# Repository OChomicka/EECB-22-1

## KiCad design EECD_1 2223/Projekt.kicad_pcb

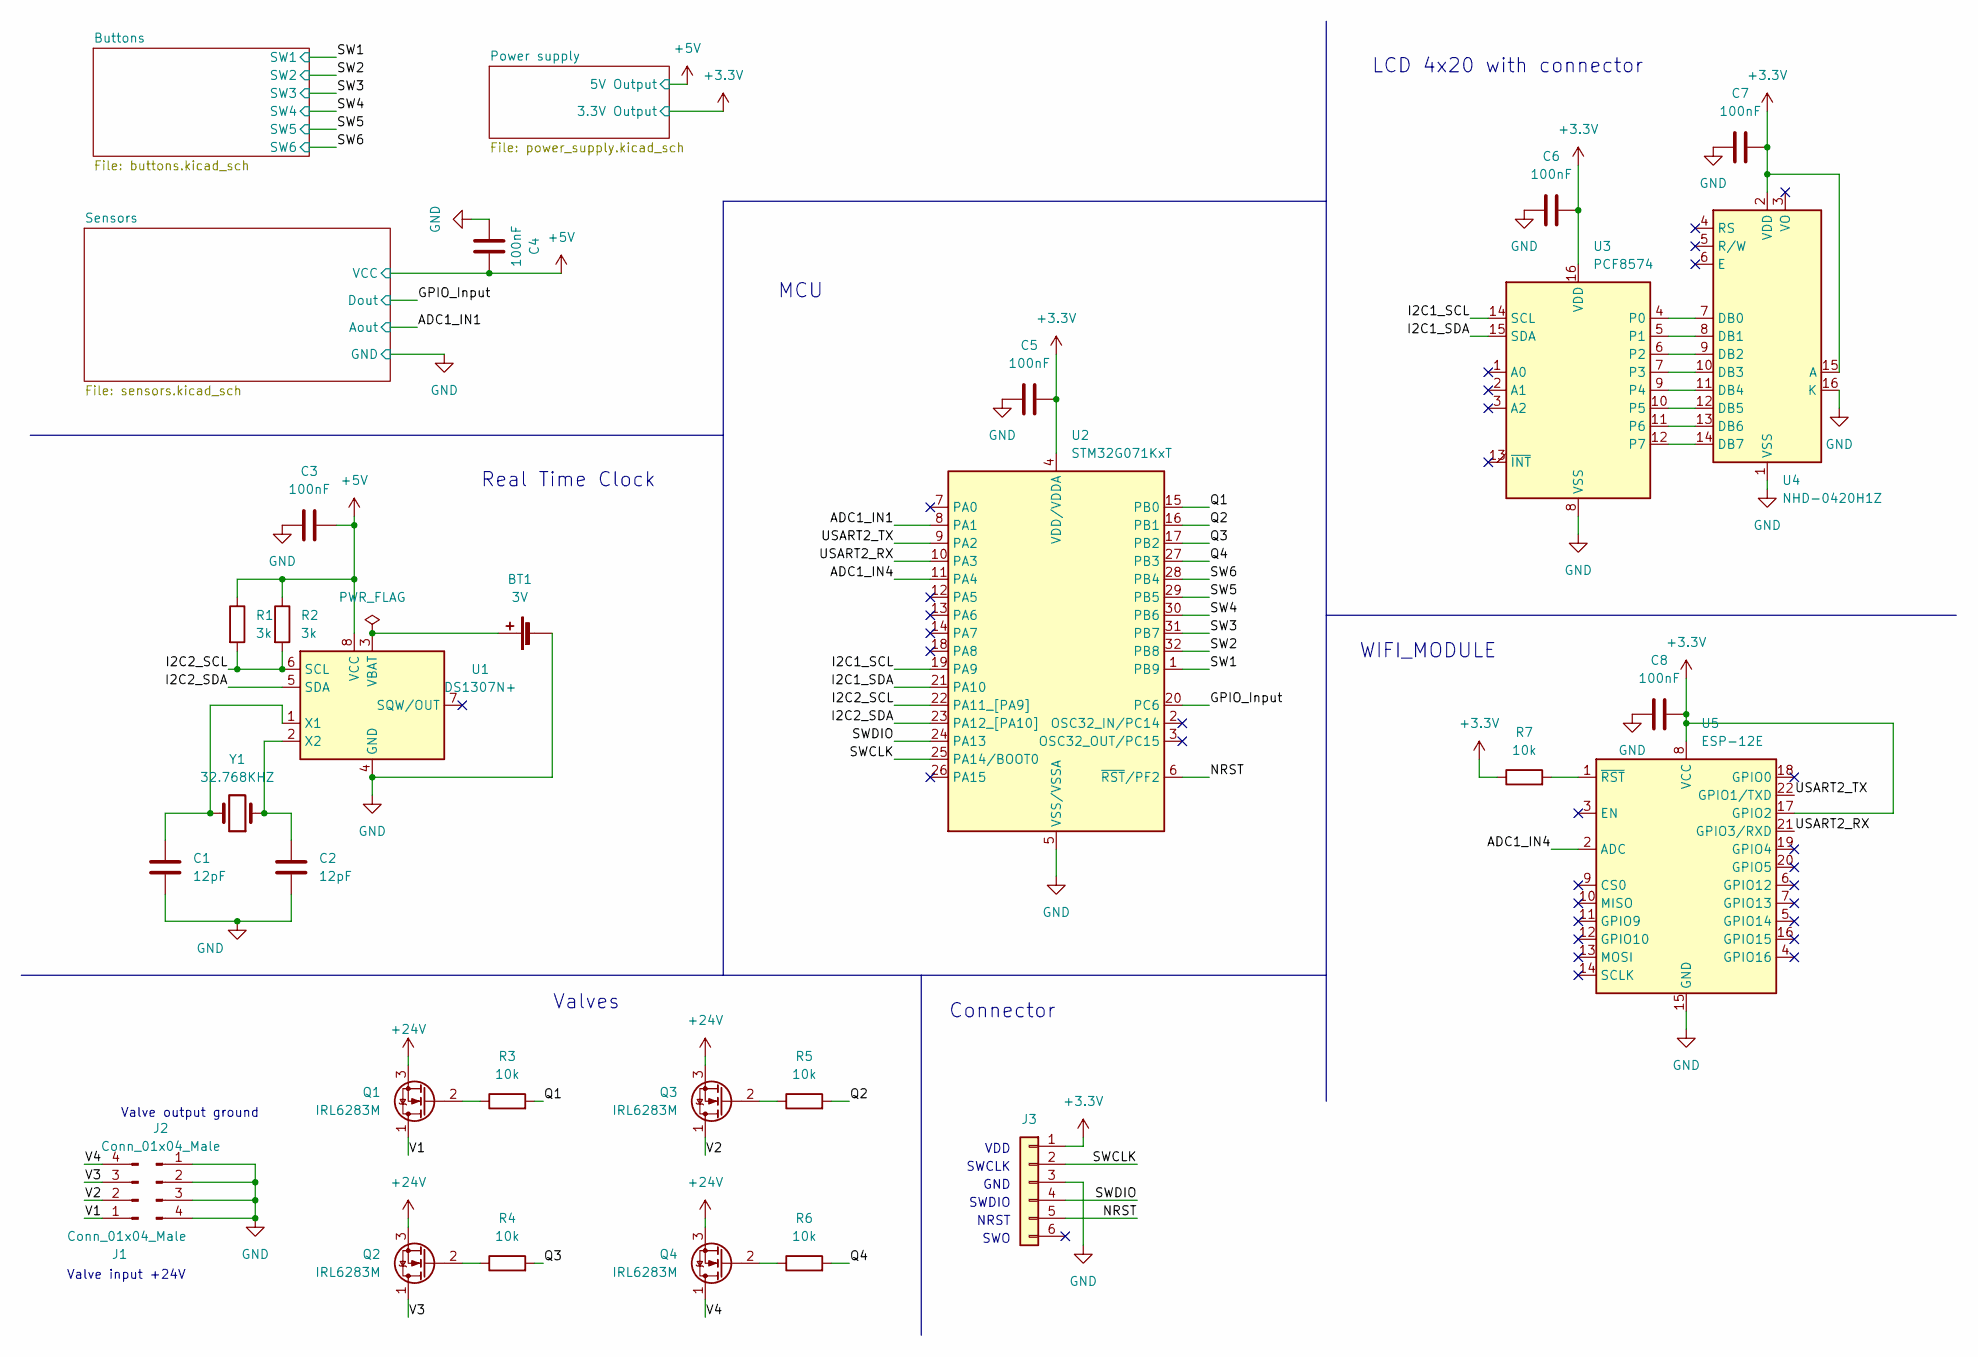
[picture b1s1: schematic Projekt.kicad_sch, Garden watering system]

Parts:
BT1: 3V; BatteryHolder_Keystone_500
C1, C2: 12pF; C_0603_1608Metric
C3, C4, C5, C6, C7, C8: 100nF; C_0603_1608Metric
J1, J2: Conn_01x04_Male; TerminalBlock_Phoenix_PT-1,5-4-3.5-H_1x04_P3.50mm_Horizontal
J3: Conn_01x06; PinHeader_1x06_P1.00mm_Vertical_SMD_Pin1Right
Q1, Q2, Q3, Q4: IRL6283M; DirectFET_MD
R1, R2: 3k; R_0603_1608Metric
R3, R4, R5, R6, R7: 10k; R_0603_1608Metric
U1: DS1307N+; SO-8_3.9x4.9mm_P1.27mm
U2: STM32G071KxT; LQFP-32_7x7mm_P0.8mm
U3: PCF8574; SO-16_3.9x9.9mm_P1.27mm
U4: NHD-0420H1Z
U5: ESP-12E
Y1: 32.768KHZ; Crystal_SMD_FOX_FQ7050-2Pin_7.0x5.0mm

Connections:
+3.3V: C5.1, C6.1, C7.1, C8.1, J3.1, R7.1, U2.4 (VDD/VDDA), U3.16 (VDD), U4.2 (VDD), U4.15 (A), U5.8 (VCC), U5.17 (GPIO2); also elsewhere on the board
+5V: C3.1, C4.1, R1.1, R2.1, U1.8 (VCC); also elsewhere on the board
+24V: Q1.3 (S), Q2.3 (S), Q3.3 (S), Q4.3 (S); also elsewhere on the board
/ADC1_IN1: U2.8 (PA1); also elsewhere on the board
/ADC1_IN4: U2.11 (PA4), U5.2 (ADC)
/GPIO_Input: U2.20 (PC6); also elsewhere on the board
/I2C1_SCL: U2.19 (PA9), U3.14 (SCL)
/I2C1_SDA: U2.21 (PA10), U3.15 (SDA)
/I2C2_SCL: R1.2, R2.2, U1.6 (SCL), U2.22 (PA11_[PA9])
/I2C2_SDA: U1.5 (SDA), U2.23 (PA12_[PA10])
/NRST: J3.5, U2.6 (~RST/PF2)
/Q1: R3.2, U2.15 (PB0)
/Q2: R5.2, U2.16 (PB1)
/Q3: R4.2, U2.17 (PB2)
/Q4: R6.2, U2.27 (PB3)
/SW1: U2.1 (PB9); also elsewhere on the board
/SW2: U2.32 (PB8); also elsewhere on the board
/SW3: U2.31 (PB7); also elsewhere on the board
/SW4: U2.30 (PB6); also elsewhere on the board
/SW5: U2.29 (PB5); also elsewhere on the board
/SW6: U2.28 (PB4); also elsewhere on the board
/SWCLK: J3.2, U2.25 (PA14/BOOT0)
/SWDIO: J3.4, U2.24 (PA13)
/USART2_RX: U2.10 (PA3), U5.21 (GPIO3/RXD)
/USART2_TX: U2.9 (PA2), U5.22 (GPIO1/TXD)
/V1: J1.1, Q1.1 (D)
/V2: J1.2, Q3.1 (D)
/V3: J1.3, Q2.1 (D)
/V4: J1.4, Q4.1 (D)
GND: BT1.2 (-), C1.2, C2.2, C3.2, C4.2, C5.2, C6.2, C7.2, C8.2, J2.1, J2.2, J2.3, J2.4, J3.3, U1.4 (GND), U2.5 (VSS/VSSA), U3.8 (VSS), U4.1 (VSS), U4.16 (K), U5.15 (GND); also elsewhere on the board
unnamed: BT1.1 (+), U1.3 (VBAT)
unnamed: C1.1, U1.1 (X1), Y1.2
unnamed: C2.1, U1.2 (X2), Y1.1
unnamed: Q1.2 (G), R3.1
unnamed: Q2.2 (G), R4.1
unnamed: Q3.2 (G), R5.1
unnamed: Q4.2 (G), R6.1
unnamed: R7.2, U5.1 (~RST)
unnamed: U3.4 (P0), U4.7 (DB0)
unnamed: U3.5 (P1), U4.8 (DB1)
unnamed: U3.6 (P2), U4.9 (DB2)
unnamed: U3.7 (P3), U4.10 (DB3)
unnamed: U3.9 (P4), U4.11 (DB4)
unnamed: U3.10 (P5), U4.12 (DB5)
unnamed: U3.11 (P6), U4.13 (DB6)
unnamed: U3.12 (P7), U4.14 (DB7)

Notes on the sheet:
Valves
VDD
SWDIO
Valve input +24V
Connector
NRST
SWCLK
MCU
Valve output ground
Real Time Clock
LCD 4x20 with connector
GND
WIFI_MODULE
SWO

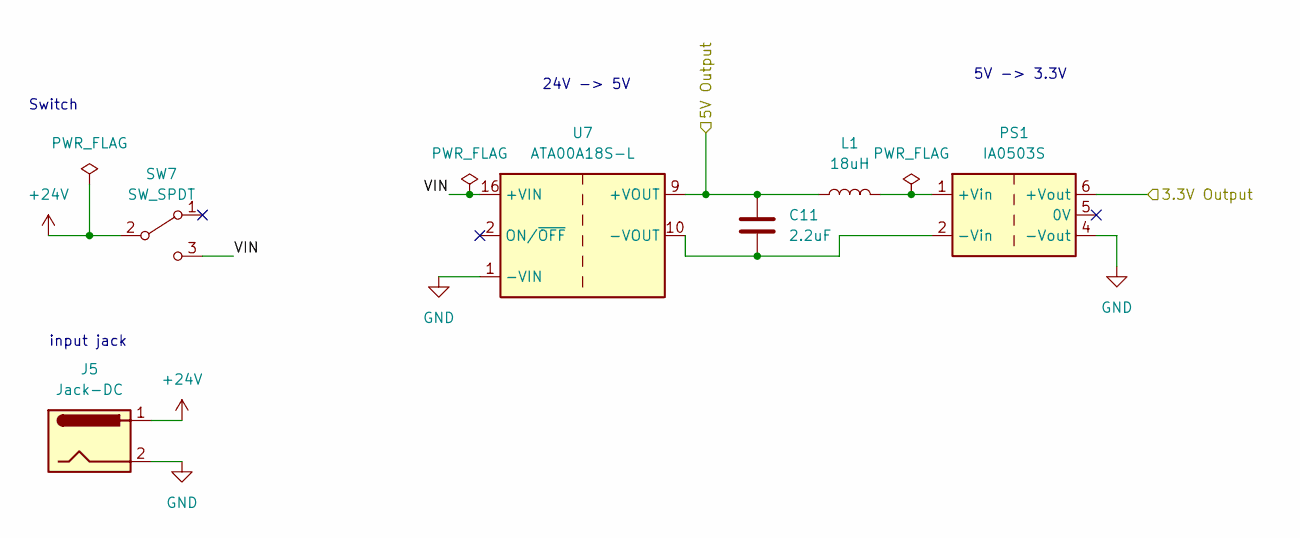
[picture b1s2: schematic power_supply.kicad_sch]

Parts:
C11: 2.2uF; C_0402_1005Metric
J5: Jack-DC; BarrelJack_CUI_PJ-063AH_Horizontal_CircularHoles
L1: 18uH; L_0603_1608Metric
PS1: IA0503S; Converter_DCDC_XP_POWER-IAxxxxS_THT
SW7: SW_SPDT; SW_Slide_1P2T_CK_OS102011MS2Q
U7: ATA00A18S-L; Converter_DCDC_Artesyn_ATA_SMD

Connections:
+3.3V: PS1.6 (+Vout); also elsewhere on the board
+5V: C11.1, L1.1, U7.9 (+VOUT); also elsewhere on the board
+24V: J5.1, SW7.2 (B); also elsewhere on the board
/Power supply/VIN: SW7.3 (C), U7.16 (+VIN)
GND: J5.2, PS1.4 (-Vout), U7.1 (-VIN); also elsewhere on the board
unnamed: C11.2, PS1.2 (-Vin), U7.10 (-VOUT)
unnamed: L1.2, PS1.1 (+Vin)

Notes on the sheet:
5V -> 3.3V
input jack
Switch
24V -> 5V

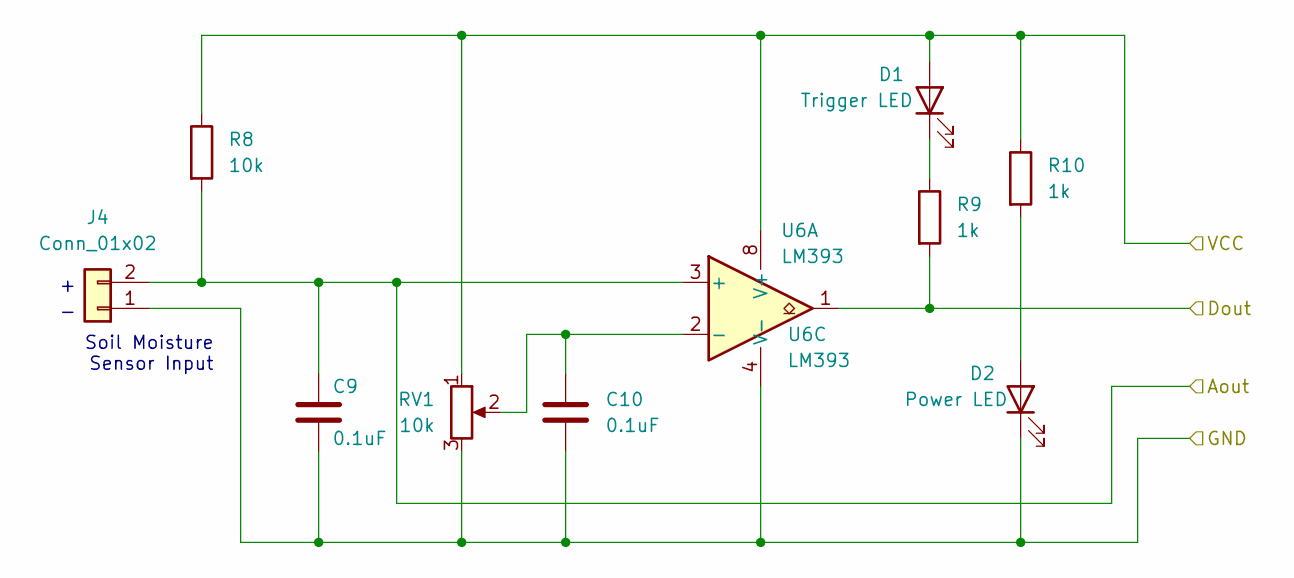
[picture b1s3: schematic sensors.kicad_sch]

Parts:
C9, C10: 0.1uF; C_0603_1608Metric
D1: Trigger LED; LED_0603_1608Metric
D2: Power LED; LED_0603_1608Metric
J4: Conn_01x02; SolderWire-0.1sqmm_1x02_P3.6mm_D0.4mm_OD1mm
R8: 10k; R_0603_1608Metric
R9, R10: 1k; R_0603_1608Metric
RV1: 10k; Potentiometer_ACP_CA6-VSMD_Vertical
U6: LM393; SOT-23-8

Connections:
+5V: D1.2 (A), R8.1, R10.1, RV1.1, U6.8 (V+); also elsewhere on the board
/ADC1_IN1: C9.1, J4.2, R8.2, U6.3 (+); also elsewhere on the board
/GPIO_Input: R9.2, U6.1; also elsewhere on the board
GND: C9.2, C10.2, D2.1 (K), J4.1, RV1.3, U6.4 (V-); also elsewhere on the board
unnamed: C10.1, RV1.2, U6.2 (-)
unnamed: D1.1 (K), R9.1
unnamed: D2.2 (A), R10.2

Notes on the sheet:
Soil Moisture Sensor Input

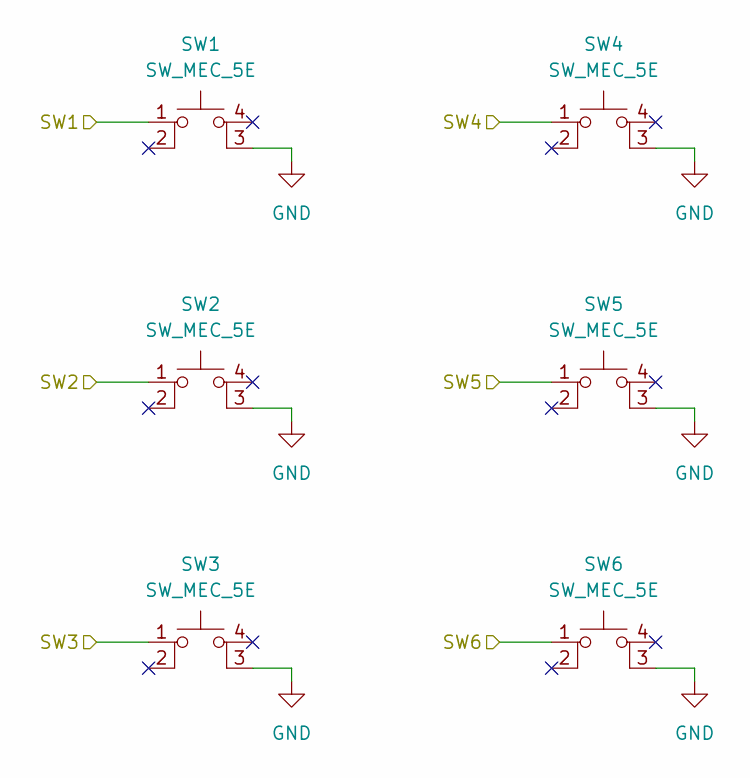
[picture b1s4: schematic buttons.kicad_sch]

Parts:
SW1, SW2, SW3, SW4, SW5, SW6: SW_MEC_5E; SW_MEC_5GSH9

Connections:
/SW1: SW1.1; also elsewhere on the board
/SW2: SW2.1; also elsewhere on the board
/SW3: SW3.1; also elsewhere on the board
/SW4: SW4.1; also elsewhere on the board
/SW5: SW5.1; also elsewhere on the board
/SW6: SW6.1; also elsewhere on the board
GND: SW1.3 (K), SW2.3 (K), SW3.3 (K), SW4.3 (K), SW5.3 (K), SW6.3 (K); also elsewhere on the board

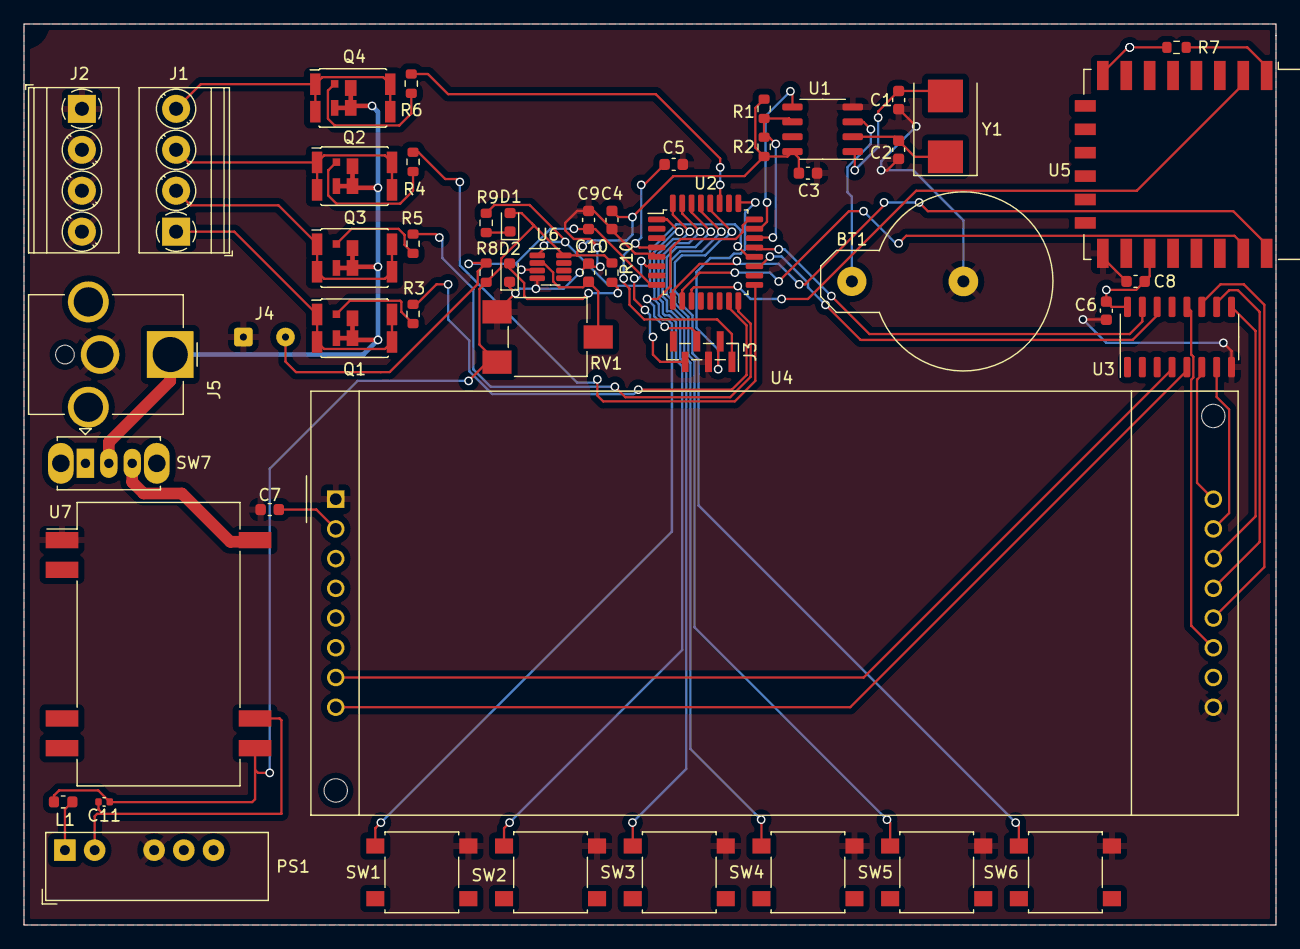
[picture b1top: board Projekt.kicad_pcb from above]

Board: 2 copper layers, 107.0 x 77.0 mm, 51 parts (0 on the bottom side), 52 nets.
